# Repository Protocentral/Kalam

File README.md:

ProtoCentral Kalam IoT
======================
 [  
 *ProtoCentral Kalam IoT (PC-4356)*](https://www.protocentral.com/iot/935-kalam-out-of-box-iot.html?search_query=kalam&results=1)

 Internet of Things or IOT is the new hot chic in the market. People seek to connect everything, from their pets to their garage doors to the Internet. The power of connected devices helps one to control it from anywhere in the world. On the other hand, Makers out there are seeking a platform that is easier to use, less cumbersome and more importantly easy on their pockets. With so many platforms out there based on the popular ESP8266, an extremely low cost WiFi module, it is indeed getting difficult for one to choose the right platform. Most commercially available modules are in the form of breakout boards. These require you to work with the limited I/O pins and more importantly will require an additional Arduino board or flashing the ESP8266 core. This can make life miserable for most makers. 

 To make it easier for developers and users alike we made a new genre of IoT platform called the OOB IoT (Out of the Box IoT)! Kalam V1 is an OOB IoT platform. It is an easy to use Arduino based platform that has an integrated ESP8266 module. Just open the box and get started on your projects without having to configure a breakout borad to work with an Arduino! 
This tiny inexpensive hulk of an IoT module in its first avatar (Kalam V1) comes as a single board with power support through USB or an external source through the RAW pin. In the second version we will introduce support for battery packs (and include a couple of battery packs) that can make your life easier as a developer/maker.

 We love our scientists and to commemorate one of the greatest scientists who also served as the most ebullient presidents of India, we aptly named our product Kalam after the late Dr. A.P.J Abdul Kalam. He chose to show the path to millions of students in India and abroad. Kindled their imaginations with his oratory skills and his writings. On occasion of his birthday we present this great platform, we hope will give the IoT space the necessary fillip. 
Inline with Make in India initiatives this is one of our first products of many we will develop, that will help makers and creators across the world!

Features Overload!
-------------------
*	Slide switch - Serial communication support to work on ESP or Atmega328 module individually
*	Firmware upgrade for ESP through USB
*	On board FTDI
*	Onboard regulator 3.3v with 800mA (with a max input of 6V)
*	Can be powered on/off using USB or external supply 
*	Board is pre-flashed  with an AT command set firmware and the same can be used to control ESP8266 module
*	Extra ESP8266 pins broken out for any additional usage requirements
*	802.11 b/g/n
*	Wi-Fi Direct (P2P), soft-AP
*	Integrated TCP/IP protocol stack

Includes:
----------
* Kalam with headers
* Micro USB type-B cable 

Repository Contents
-------------------
* **/Firmware**  - Firmware and bin files for ESP8266
* **/Libraries** - Arduino library and example sketches.
* **/Hardware**  - All Eagle design files (.brd, .sch)

License Information
-------------------
This product is open source!

Please use, reuse, and modify these files as you see fit. Please maintain attribution to Protocentral and release anything derivative under the same license.

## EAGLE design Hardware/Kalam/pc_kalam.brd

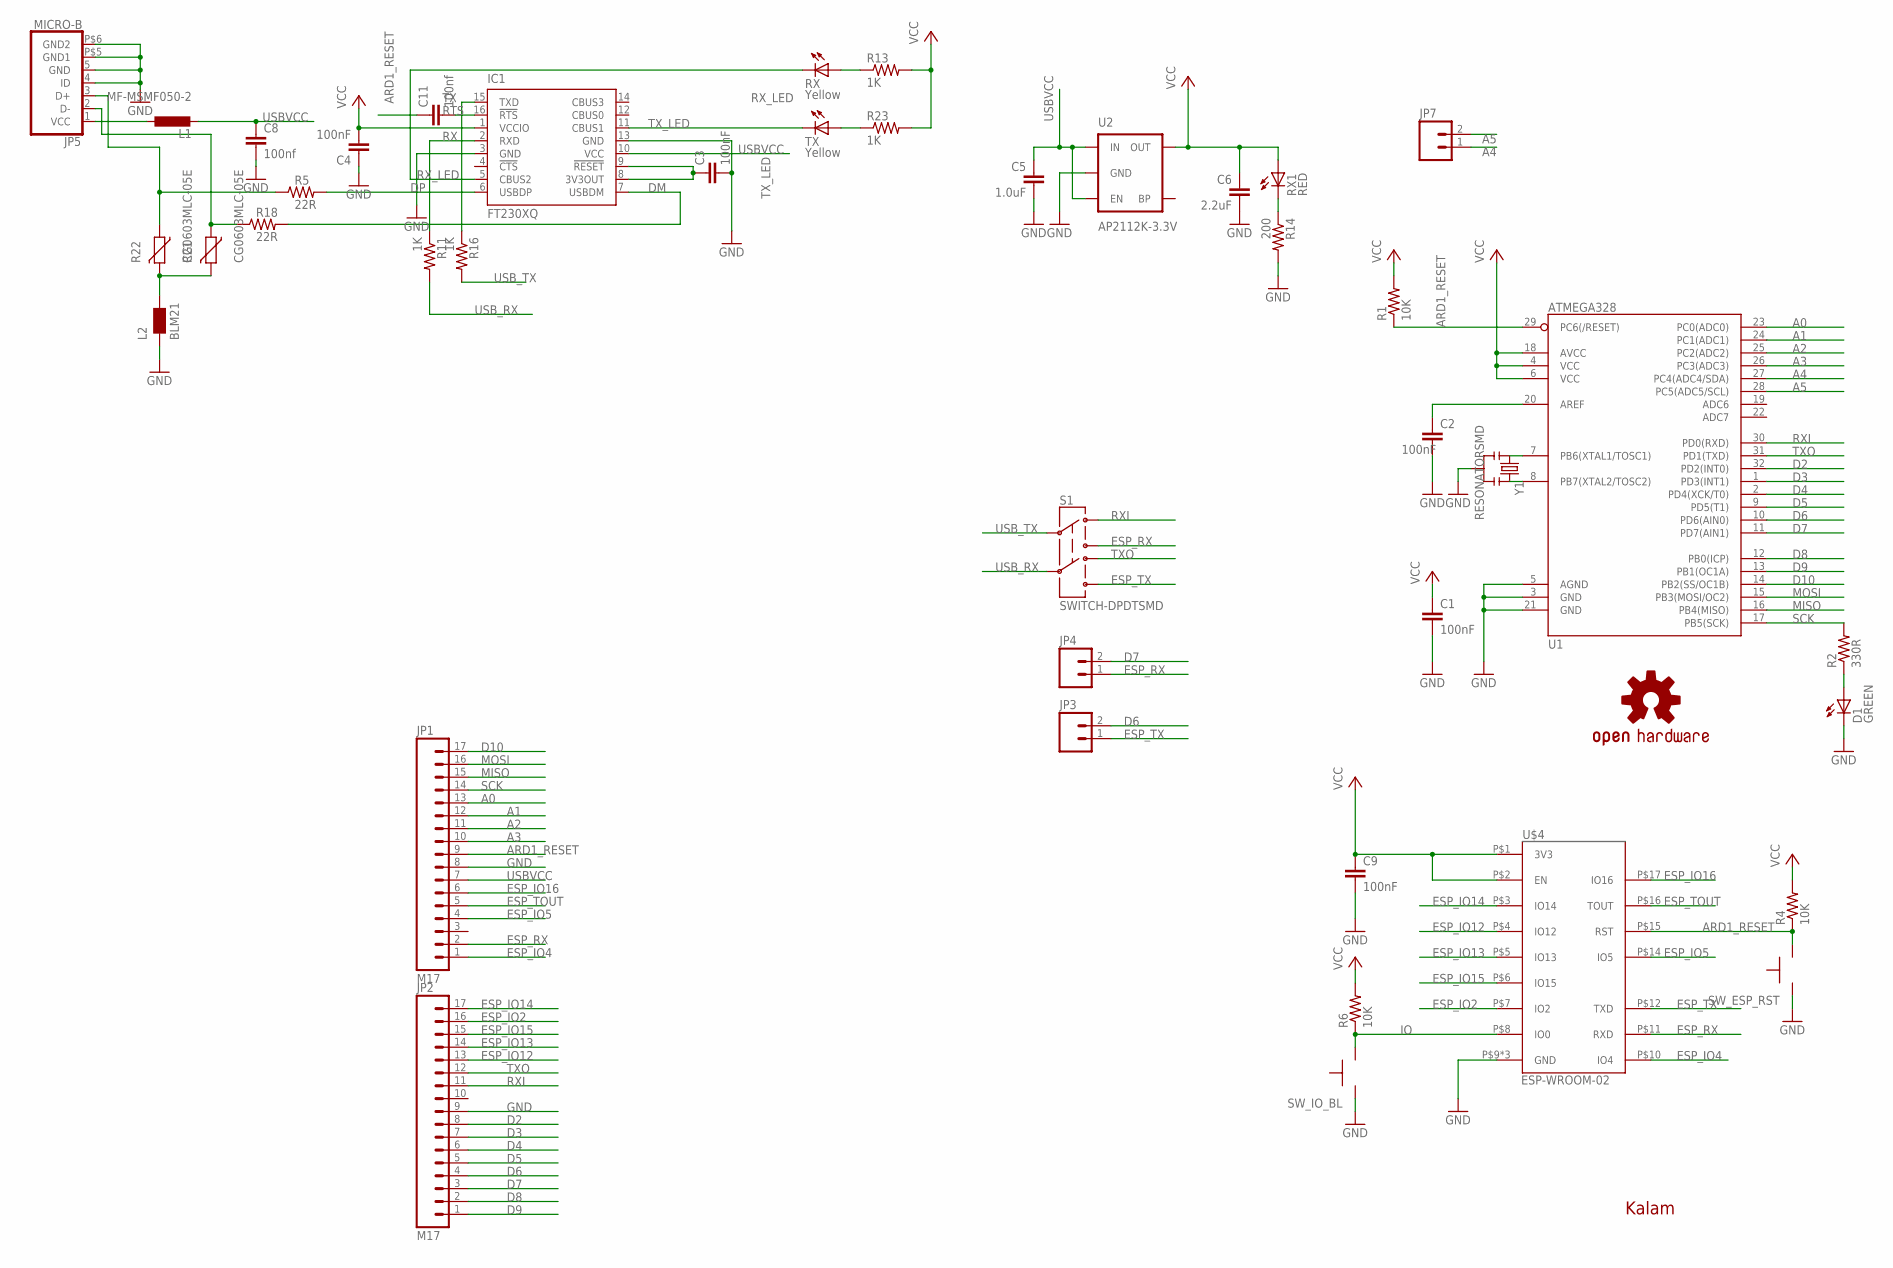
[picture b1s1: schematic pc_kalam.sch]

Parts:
C1, C2, C9: 100nF; C0402
C3, C4: 100nF; C0805
C5: 1.0uF; 0805
C6: 2.2uF; C0805
C8, C11: 100nf; C0805
D1: GREEN; LED-0603
IC1: FT230XQ; QFN16
JP1, JP2: M17; 1X17
JP3, JP4, JP7: M02PTH; 1X02
JP5: MICRO-B
L1: MF-MSMF050-2; L1812
L2: BLM21; 0805
R1, R4, R6: 10K; R0402
R2: 330R; R0402
R5, R18: 22R; R0805
R11, R13, R16, R23: 1K; R0805
R14: 200; R0805
R21, R22: CG0603MLC-05E; CT/CN0603
RX: Yellow; CHIPLED_0603
RX1: RED; CHIPLED_0603
S1: SWITCH-DPDTSMD; AYZ0202
SW_ESP_RST: B3U-1000P
SW_IO_BL: B3U-1000P
TX: Yellow; CHIPLED_0603
U1: ATMEGA328; TQFP32-08
U2: AP2112K-3.3V; SOT23-5
U$1: OSHW-LOGOS; OSHW-LOGO-S
U$2, U$3: PROTY-LOGO; LOGO-PROTY
U$4: ESP-WROOM-02
U$5: KALAM
Y1: RESONATORSMD; RESONATOR-SMD

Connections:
A0: JP1.13, U1.23 (PC0(ADC0))
A1: JP1.12, U1.24 (PC1(ADC1))
A2: JP1.11, U1.25 (PC2(ADC2))
A3: JP1.10, U1.26 (PC3(ADC3))
A4: JP7.1, U1.27 (PC4(ADC4/SDA))
A5: JP7.2, U1.28 (PC5(ADC5/SCL))
ARD1_RESET: C11.1, JP1.9, R1.1, R4.1, SW_ESP_RST.P$2, U1.29 (PC6(/RESET)), U$4.P$15 (RST)
D2: JP2.8, U1.32 (PD2(INT0))
D3: JP2.7, U1.1 (PD3(INT1))
D4: JP2.6, U1.2 (PD4(XCK/T0))
D5: JP2.5, U1.9 (PD5(T1))
D6: JP2.4, JP3.2, U1.10 (PD6(AIN0))
D7: JP2.3, JP4.2, U1.11 (PD7(AIN1))
D8: JP2.2, U1.12 (PB0(ICP))
D9: JP2.1, U1.13 (PB1(OC1A))
D10: JP1.17, U1.14 (PB2(SS/OC1B))
DM: IC1.7 (USBDM), R18.2
DP: IC1.6 (USBDP), R5.2
ESP_IO2: JP2.16, U$4.P$7 (IO2)
ESP_IO4: JP1.1, U$4.P$10 (IO4)
ESP_IO5: JP1.4, U$4.P$14 (IO5)
ESP_IO12: JP2.13, U$4.P$4 (IO12)
ESP_IO13: JP2.14, U$4.P$5 (IO13)
ESP_IO14: JP2.17, U$4.P$3 (IO14)
ESP_IO15: JP2.15, U$4.P$6 (IO15)
ESP_IO16: JP1.6, U$4.P$17 (IO16)
ESP_RX: JP1.2, JP4.1, S1.3, U$4.P$11 (RXD)
ESP_TOUT: JP1.5, U$4.P$16 (TOUT)
ESP_TX: JP3.1, S1.6, U$4.P$12 (TXD)
GND: C1.2, C2.2, C3.2, C4.1, C5.2, C6.2, C8.2, C9.2, D1.C, IC1.3 (GND), IC1.13 (GND), JP1.8, JP2.9, JP5.4 (ID), JP5.5 (GND), JP5.P$5 (GND1), JP5.P$6 (GND2), L2.1, R14.2, SW_ESP_RST.P$1, SW_IO_BL.P$1, U1.3 (GND), U1.5 (AGND), U1.21 (GND), U2.2 (GND), U$4.P$9 (GND), U$4.P$13 (GND), U$4.P$18 (GND), Y1.2
IO: R6.1, SW_IO_BL.P$2, U$4.P$8 (IO0)
MISO: JP1.15, U1.16 (PB4(MISO))
MOSI: JP1.16, U1.15 (PB3(MOSI/OC2))
unnamed: C2.1, U1.20 (AREF)
unnamed: U1.8 (PB7(XTAL2/TOSC2)), Y1.3
unnamed: U1.7 (PB6(XTAL1/TOSC1)), Y1.1
unnamed: C3.1, IC1.8 (3V3OUT), IC1.9 (!RESET)
unnamed: R14.1, RX1.C
unnamed: D1.A, R2.1
unnamed: JP5.2 (D-), R18.1, R21.1
unnamed: JP5.1 (VCC), L1.1
unnamed: R13.1, RX.A
unnamed: R23.1, TX.A
unnamed: L2.2, R21.2, R22.2
unnamed: JP5.3 (D+), R5.1, R22.1
RTS: C11.2, IC1.16 (!RTS)
RX: IC1.2 (RXD), R11.1
RXI: JP2.11, S1.1, U1.30 (PD0(RXD))
RX_LED: IC1.5 (CBUS2), RX.C
SCK: JP1.14, R2.2, U1.17 (PB5(SCK))
TX: IC1.15 (TXD), R16.1
TXO: JP2.12, S1.4, U1.31 (PD1(TXD))
TX_LED: IC1.11 (CBUS1), TX.C
USBVCC: C5.1, C8.1, IC1.10 (VCC), JP1.7, L1.2, U2.1 (IN), U2.3 (EN)
USB_RX: R11.2, S1.5
USB_TX: R16.2, S1.2
VCC: C1.1, C4.2, C6.1, C9.1, IC1.1 (VCCIO), R1.2, R4.2, R6.2, R13.2, R23.2, RX1.A, U1.4 (VCC), U1.6 (VCC), U1.18 (AVCC), U2.5 (OUT), U$4.P$1 (3V3), U$4.P$2 (EN)

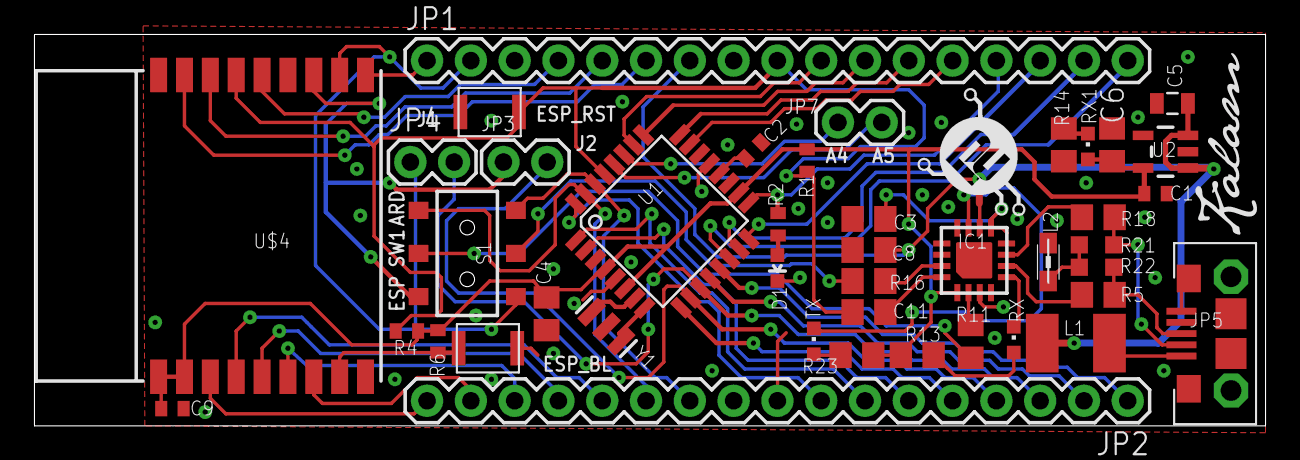
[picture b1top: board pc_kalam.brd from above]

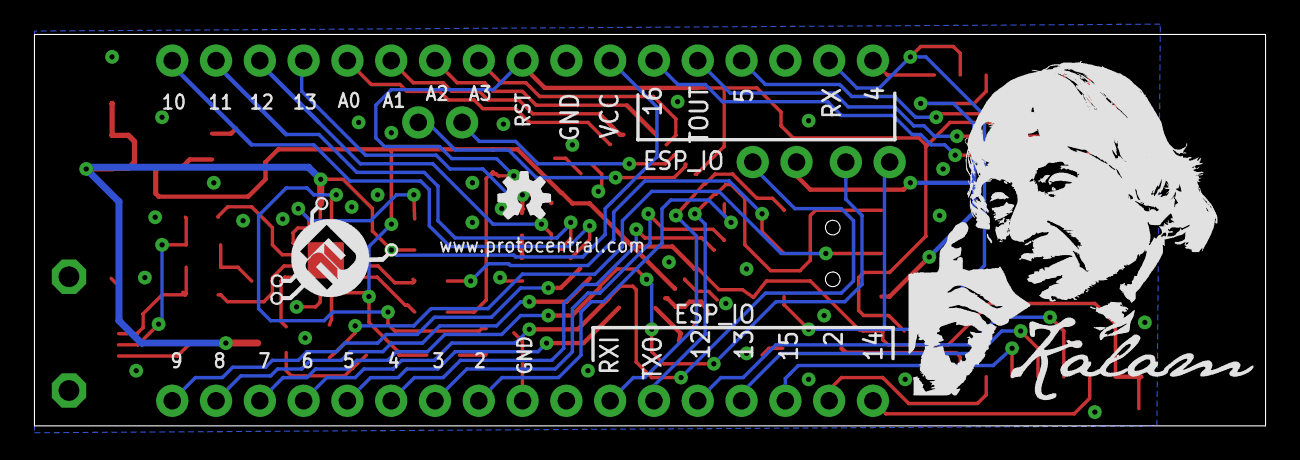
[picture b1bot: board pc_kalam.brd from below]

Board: 4 copper layers, 71.4 x 22.7 mm, 47 parts (3 on the bottom side), 57 nets.

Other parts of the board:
U$6: KALAM-NAME-ONLY

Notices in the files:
parts and their libraries:
SparkFun-Capacitors: Licensing: Creative Commons ShareAlike 4.0 International - https://creativecommons.org/licenses/by-sa/4.0
